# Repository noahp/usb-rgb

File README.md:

# 🔆 usb connected rgb led
Inspired by https://github.com/todbot/blink1 , this is a respun clone that adds a
single capacitive touch pad for input.

# Hardware
See files under [hw](hw).

* *TODO* bom
* *TODO* schematic
* *TODO* pcb / 3d render

## Reference
SAMD11 manual:
>http://ww1.microchip.com/downloads/en/DeviceDoc/Atmel-42363-SAM-D11_Datasheet.pdf

Digikey SAMD11D14A part:
>https://www.digikey.com/short/jwwn7f

The PIC16F1454 (similar to the PIC16F1455 used by blink(1)) is about $0.03-$0.05 cheaper
at qty=1 ([SAMD11D14A](https://octopart.com/search?q=ATSAMD11D14A) vs
[PIC16F1454](https://octopart.com/search?q=PIC16F1454)):
>https://www.digikey.com/short/jwnprd

SAMD11 is a little more appealing for:
1. open toolchain (arm-none-eabi-gcc)
2. SWD debug interface
3. built in capsense hw (not a huge deal)

PIC16F1454 however doesn't require a 5v->3.3v regulator which is nice.

### EFM32HG309F64G
Another Cortex M0 with USB, this one's got an on-chip 5v->3.3v regulator and a ROM USB (CDC serial) bootloader which is appealing:
>https://www.digikey.com/short/jnh91h

>https://www.silabs.com/documents/public/data-sheets/efm32hg-datasheet.pdf

# Firmware
See files under [fw](fw).

Reference:
>ASF mirror: https://github.com/avrxml/asf

* *TODO* samd11d usb application

# Software
See files under [sw](sw).

*TODO*
This repo provides a python (2/3 compatible) module for interfacing the device.

Install via:
```bash
pip install sw
```

Whoami test via:
```bash
python3 -c "from noahp_usb_rgb import Usbrgb; print(Usbrgb().get_version())"
```

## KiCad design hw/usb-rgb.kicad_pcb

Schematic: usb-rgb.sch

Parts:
C1, C2: C; C_0603_1608Metric_Pad1.05x0.95mm_HandSolder
D1: WS2812B; LED_WS2812B_PLCC4_5.0x5.0mm_P3.2mm
J1: Conn_01x05_Female; SMD_JST_5_PIN_VERT
J2: USB_B_Micro; usb_micro_b_smt
R1: R; R_0603_1608Metric_Pad1.05x0.95mm_HandSolder
R2: R22; R_0603_1608Metric_Pad1.05x0.95mm_HandSolder
R3: R10; R_0603_1608Metric_Pad1.05x0.95mm_HandSolder
TP1, TP2: TestPoint; TEST_0.100
U1: SAMD11D14A-M; QFN-24-1EP_4x4mm_P0.5mm_EP2.6x2.6mm
U2: MCP1700-3302E_SOT23; SOT-23

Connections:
/mcu_usbdm: R1.2, U1.21 (PA24)
/mcu_usbdp: R2.1, U1.22 (PA25)
/rgb_ctl: D1.4, R3.1
/sercom0-pad[0]: R3.2, U1.5 (PA06)
/swclk: J1.3, U1.19 (PA30/SWCLK)
/swdio: J1.2, U1.20 (PA31/SWDIO)
/touch_sns: TP2.1, U1.1 (PA02)
/usb_dm: J2.2, R2.2
/usb_dp: J2.3, R1.1
/usb_sof_pin: TP1.1, U1.16 (PA23)
/usb_vbus: C1.1, D1.1, J2.1, U2.3 (VI)
/vdd: C2.1, J1.1, U1.24 (VDD), U2.2 (VO)
/~rst: J1.4, U1.18 (PA28/~RST)
GND: C1.2, C2.2, D1.3, J1.5, J2.5, U1.23 (GND), U2.1 (GND)

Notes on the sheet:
swd debug header
usb connector modes 1. usb micro b physical connector 2. usb a male pcb pad only connector (board inserts to usb a host port)
ldo 5v -> 3.3v regulator
nopop
rgb led out vin nominal 5v i/o works with 3.3v

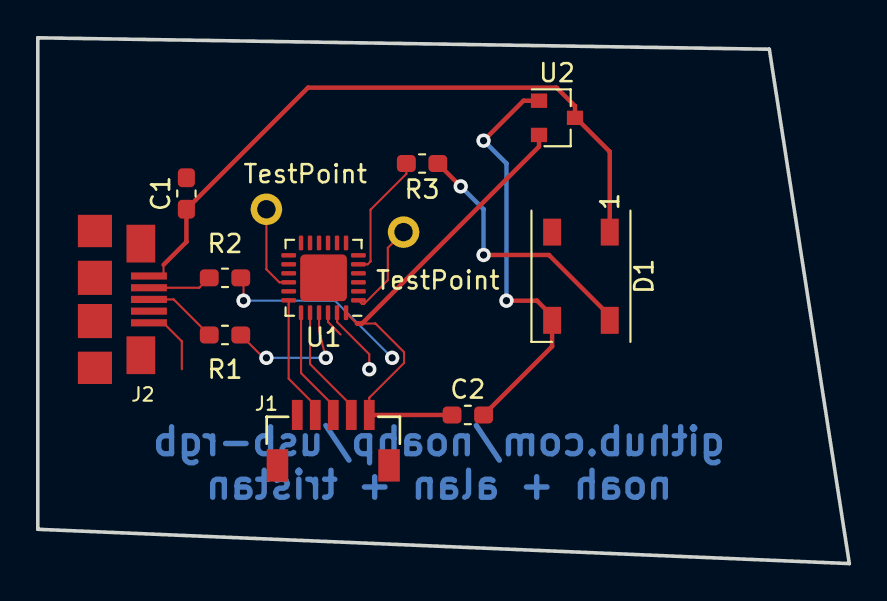
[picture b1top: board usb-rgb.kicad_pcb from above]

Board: 2 copper layers, 45.1 x 29.2 mm, 12 parts (0 on the bottom side), 14 nets.

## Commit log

2018-09-22 ✨ first check in, readme and blank hw files
2018-09-22 ✨ schematic done for now
2018-10-01 🏁 pcb race entry
